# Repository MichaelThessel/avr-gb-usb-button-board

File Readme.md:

Repository for Game Boy USB button board

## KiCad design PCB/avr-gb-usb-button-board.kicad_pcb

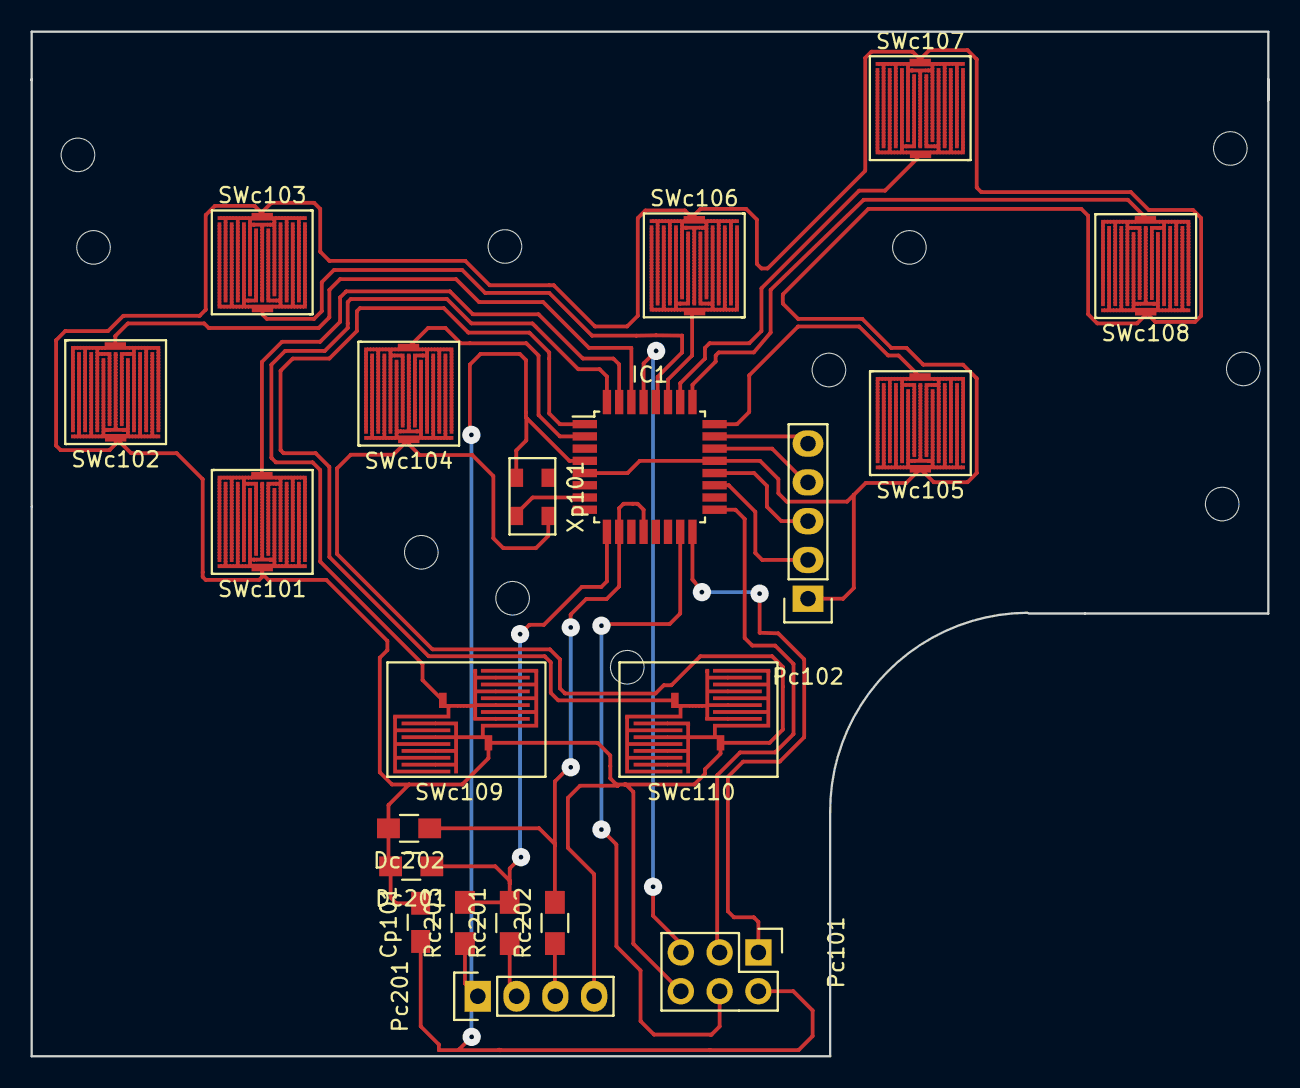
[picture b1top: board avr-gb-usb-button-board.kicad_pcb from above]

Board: 2 copper layers, 81.0 x 67.1 mm, 21 parts (0 on the bottom side), 25 nets.

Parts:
Cp101: 10uF; C_0805_HandSoldering
Dc201, Dc202: 3V6; R_0805_HandSoldering
IC1: ATTINY88-A; TQFP-32_7x7mm_Pitch0.8mm
Pc101: CONN_02X03; Pin_Header_Straight_2x03
Pc102: CONN_01X05; Pin_Header_Straight_1x05
Pc201: CONN_01X04; Pin_Header_Straight_1x04
Rc201, Rc202: 47R; R_0805_HandSoldering
Rc203: 2k; R_0805_HandSoldering
SWc101, SWc102, SWc103, SWc104, SWc105, SWc106, SWc107, SWc108: SW_PUSH; GBButtonPad5mm
SWc109, SWc110: SW_PUSH; GBButtonPad3mm
Xp101: CRYSTAL_SMD; KC5032A12.0000CMGE00

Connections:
GND: Cp101.2, Dc201.2, Dc202.2, IC1.5, IC1.21, Pc101.6, Pc102.1, Pc201.4, SWc101.2, SWc102.2, SWc103.2, SWc104.2, SWc105.2, SWc106.2, SWc107.2, SWc108.2, SWc109.2, SWc110.2, Xp101.2
unnamed: Dc201.1, IC1.9, Rc201.2, Rc203.2
unnamed: Dc202.1, IC1.10, IC1.12, Rc202.2
unnamed: IC1.1, SWc110.1
unnamed: IC1.2, SWc104.1
unnamed: IC1.7, Xp101.3
unnamed: IC1.15, Pc101.4
unnamed: IC1.16, Pc101.1
unnamed: IC1.17, Pc101.3
unnamed: IC1.19, Pc102.2
unnamed: IC1.20, Pc102.3
unnamed: IC1.22, Pc102.4
unnamed: IC1.23, Pc102.5
unnamed: IC1.24, SWc105.1
unnamed: IC1.25, SWc108.1
unnamed: IC1.26, SWc107.1
unnamed: IC1.27, SWc106.1
unnamed: IC1.28, SWc103.1
unnamed: IC1.29, Pc101.5
unnamed: IC1.30, SWc102.1
unnamed: IC1.31, SWc101.1
unnamed: IC1.32, SWc109.1
unnamed: Pc201.2, Rc201.1
unnamed: Pc201.3, Rc202.1
VCC: Cp101.1, IC1.4, Pc101.2, Pc201.1, Rc203.1, Xp101.1

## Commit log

2016-05-06 Added PCB outline
2016-05-06 Changed ground plane
2016-05-08 Removed library
2016-05-08 Added buttons to schema
2016-05-08 Added mounting holes
2016-05-08 Added button footprint
2016-05-09 Added ABXY button markers
2016-05-09 Updated 5mm button footprint
2016-05-09 Added 3mm button footprint
2016-05-09 Placed start and select buttons
2016-05-09 Wired buttons
2016-05-09 Connected VCC
2016-05-09 Wired ISP header
2016-05-11 Added oscillator
2016-05-11 Added USB connector
